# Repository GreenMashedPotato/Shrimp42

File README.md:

# Shrimp42(previously Kibod-01) Work In Progress

it's a keyboard inspired by [Slepet](https://github.com/ibnuda/Slepet) that has more stagger in some columns and only 3 thumb cluster keys instead of 5.

## Rev 1 (initial prototype)
Non Mirrored Keyboard uses 1 pro micro with 2x5 10pin IDC Connector:

Mirrored Keyboard, supports using 2 pro micros with trrs, or 1 pro micro with 2x5 10pin IDC Connector:

## Rev 2
Mirrored Keyboard Rev2(renamed to Shrimp42):

improvements from rev1:

* adds support for hotswap sockets
* adds support for smd diodes
* changed angles from 2 to 3 degrees while reducing distance between columns. 
* add board name: Shrimp 42
* add Stacked Acrylic Case

V1 vs V2

## Materials

| Qnty | Ref | Value | Description |
| --- | --- | --- | --- |
| 1 (2 if using trrs) | U1 | Arduino Pro-Micro ATmega32U4 |
| 42 | D-0-0 - D-3-5 | 1N4148 | Diode: 1N4148 (SOD 123 or THT)|
| 42 | K-0-0 - K-3-5 | MX or ALPS Switches | 1U |
| 42 (optional) | K-0-0 - K-3-5 | MX or ALPS Hotswap Sockets | this board supports the use of hotswap sockets and soldered connections |
| 2 | U2 | TRRS connectors OR 2x5 10pin IDC Connector |
| 1 | | TRRS Cable OR 2x5 10pin IDC Cable | used to connect both halves |
| 2 | | Shrimp42 pcb |
 
## Firmware
QMK and VIAL (provided via firmware but will need to sideload json and is untested) firmware for using the keyboard like in my setup above (using the extended GPIO pin to connect both halves and only 1 pro micro). [here](https://github.com/GreenMashedPotato/vial-qmk/tree/Shrimp42/keyboards/shrimp42).
 
QMK and VIAL for trrs connection (using 2 pro micros, slave board flipped, trrs connecting both sides) [here](https://github.com/GreenMashedPotato/vial-qmk/tree/Shrimp42/keyboards/shrimp42trrs)

## Library Used
[Keebio's footprints](https://github.com/keebio/Keebio-Parts.pretty)
[Ibnuda's footprints](https://github.com/ibnuda/rick-kicad-libs)

## Contact me:
Reddit [u/greenmashedpotato](https://www.reddit.com/user/greenmashedpotato)

## Disclaimer

I don't reccomend trying rev1 since the innermost and outermost column may be too far for some hands and can be tiring to use for long durations.

I haven't printed some of it. No guarantees that they work.

If things go wrong, I won't take any responisibilities, Try at your own risk.

## Additional Notes
After using the 2 in 1 diodes footprint, it may be too hard to know the orientation.
make sure the line on the diode is facing the square hole:

When using the Extended gpio pins to connect both halves, I have only tested using the pro micro on the left.

When using TRRS, dont forget to flip the right pro micro, I have only tested using the left pro micro as Master.

## License
GPL-3.0 License

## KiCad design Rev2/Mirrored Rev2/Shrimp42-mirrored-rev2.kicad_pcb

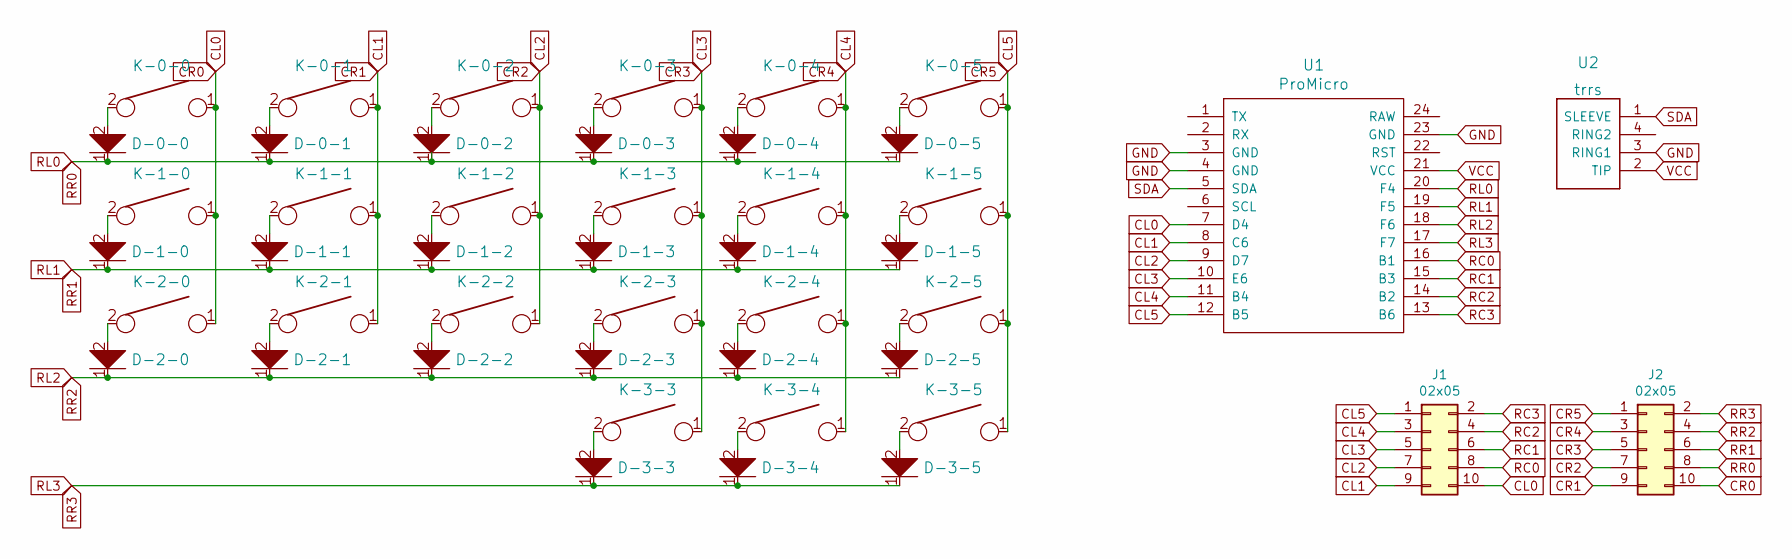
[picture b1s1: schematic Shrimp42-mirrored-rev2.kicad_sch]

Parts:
D-0-0, D-0-1, D-0-2, D-0-3, D-0-4, D-0-5, D-1-0, D-1-1, D-1-2, D-1-3, D-1-4, D-1-5, D-2-0, D-2-1, D-2-2, D-2-3, D-2-4, D-2-5, D-3-3, D-3-4, D-3-5: D; Diode-dual
J1, J2: 02x05; connector-shrouded
K-0-0, K-0-1, K-0-2, K-0-3, K-0-4, K-0-5, K-1-0, K-1-1, K-1-2, K-1-3, K-1-4, K-1-5, K-2-0, K-2-1, K-2-2, K-2-3, K-2-4, K-2-5, K-3-3, K-3-4, K-3-5: KEYSW; 100-dual-socket
U1: ProMicro; promicro
U2: trrs

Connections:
CL0: J1.10, J2.10, K-0-0.1, K-1-0.1, K-2-0.1, U1.7 (D4)
CL1: J1.9, J2.9, K-0-1.1, K-1-1.1, K-2-1.1, U1.8 (C6)
CL2: J1.7, J2.7, K-0-2.1, K-1-2.1, K-2-2.1, U1.9 (D7)
CL3: J1.5, J2.5, K-0-3.1, K-1-3.1, K-2-3.1, K-3-3.1, U1.10 (E6)
CL4: J1.3, J2.3, K-0-4.1, K-1-4.1, K-2-4.1, K-3-4.1, U1.11 (B4)
CL5: J1.1, J2.1, K-0-5.1, K-1-5.1, K-2-5.1, K-3-5.1, U1.12 (B5)
GND: U1.3 (GND), U1.4 (GND), U1.23 (GND), U2.3 (RING1)
unnamed: D-0-0.2, K-0-0.2
unnamed: D-0-1.2, K-0-1.2
unnamed: D-0-2.2, K-0-2.2
unnamed: D-0-3.2, K-0-3.2
unnamed: D-0-4.2, K-0-4.2
unnamed: D-0-5.2, K-0-5.2
unnamed: D-1-0.2, K-1-0.2
unnamed: D-1-1.2, K-1-1.2
unnamed: D-1-2.2, K-1-2.2
unnamed: D-1-3.2, K-1-3.2
unnamed: D-1-4.2, K-1-4.2
unnamed: D-1-5.2, K-1-5.2
unnamed: D-2-0.2, K-2-0.2
unnamed: D-2-1.2, K-2-1.2
unnamed: D-2-2.2, K-2-2.2
unnamed: D-2-3.2, K-2-3.2
unnamed: D-2-4.2, K-2-4.2
unnamed: D-2-5.2, K-2-5.2
unnamed: D-3-3.2, K-3-3.2
unnamed: D-3-4.2, K-3-4.2
unnamed: D-3-5.2, K-3-5.2
RC0: J1.8, U1.16 (B1)
RC1: J1.6, U1.15 (B3)
RC2: J1.4, U1.14 (B2)
RC3: J1.2, U1.13 (B6)
RL0: D-0-0.1, D-0-1.1, D-0-2.1, D-0-3.1, D-0-4.1, D-0-5.1, J2.8, U1.20 (F4)
RL1: D-1-0.1, D-1-1.1, D-1-2.1, D-1-3.1, D-1-4.1, D-1-5.1, J2.6, U1.19 (F5)
RL2: D-2-0.1, D-2-1.1, D-2-2.1, D-2-3.1, D-2-4.1, D-2-5.1, J2.4, U1.18 (F6)
RL3: D-3-3.1, D-3-4.1, D-3-5.1, J2.2, U1.17 (F7)
SDA: U1.5 (SDA), U2.1 (SLEEVE)
VCC: U1.21 (VCC), U2.2 (TIP)

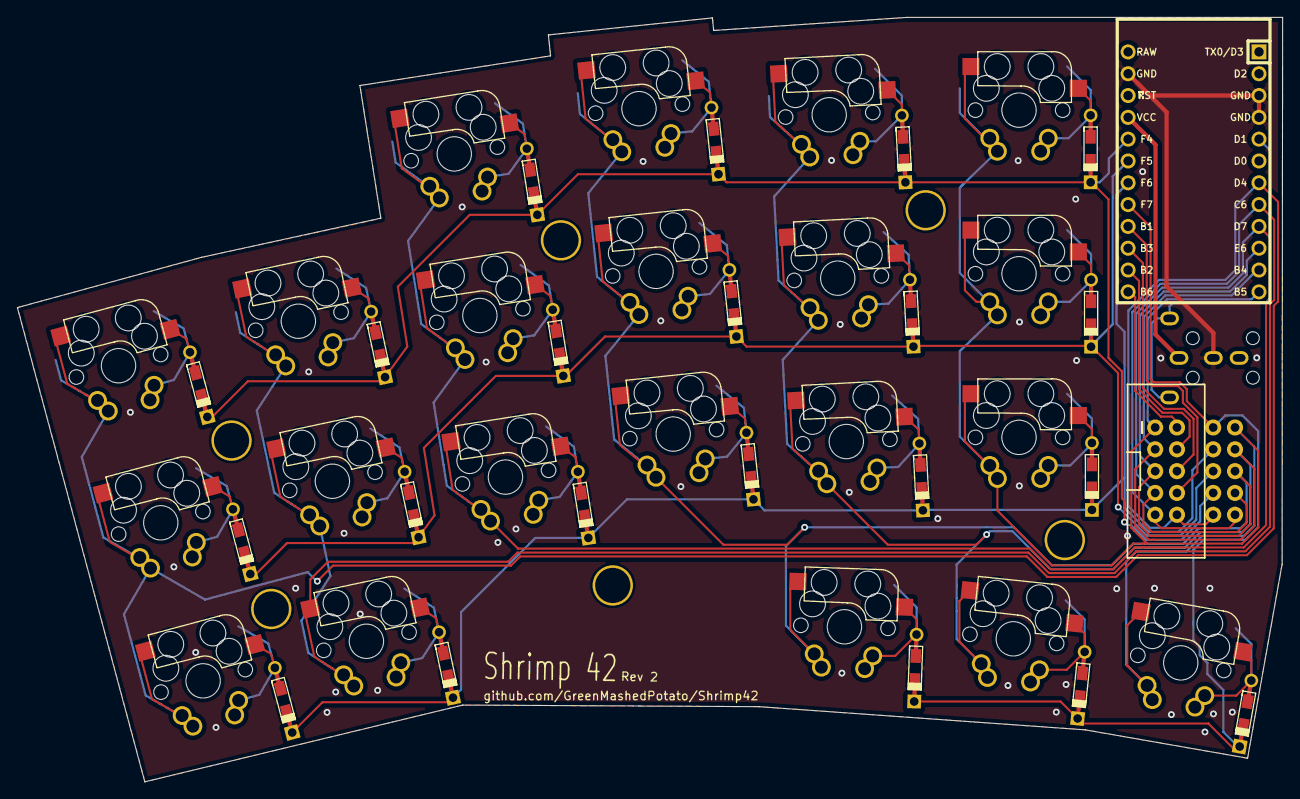
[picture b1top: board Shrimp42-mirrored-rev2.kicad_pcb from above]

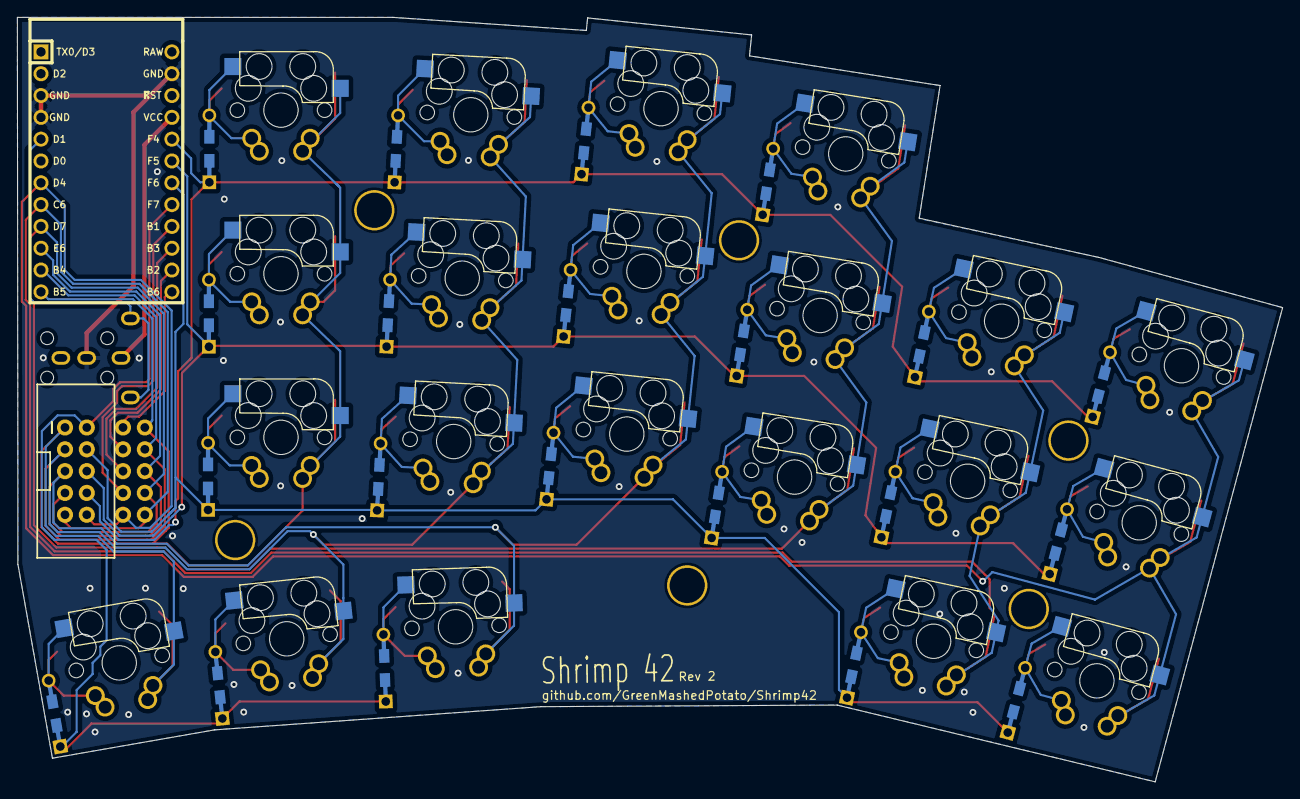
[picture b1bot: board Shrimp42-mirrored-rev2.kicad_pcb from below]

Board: 2 copper layers, 147.3 x 89.0 mm, 52 parts (2 on the bottom side), 38 nets.

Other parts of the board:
Ref**1, Ref**2, Ref**3, Ref**4, Ref**5, Ref**6: Val**; HOLE_M2_TH

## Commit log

2022-01-05 First Design
2022-01-05 add gerber
2022-01-05 fix outline issue
2022-01-05 add readme
2022-01-05 cleanup svgs
2022-01-05 add copper layer
2022-01-05 fix minor issues
2022-01-05 add warning
2022-01-05 move files to default folder
2022-01-05 add mirrored
2022-01-05 fix gerber error jlcpcb
2022-01-06 Create LICENSE
2022-01-06 add mirror to readme
2022-01-06 fix typo
2022-01-17 renamed mirrored
2022-01-25 fixed non reversible holes
2022-01-29 update gerber and readme
2022-01-29 add more detail to readme
2022-01-29 update gitignore
2022-01-29 removed case svg, will readd after fixing it.
2022-01-31 update readme, working on rev2
2022-02-04 add rev2
2022-02-05 add name and icon, add mounting holes, add trrs support back
2022-02-05 cleanup some wiring
2022-02-06 update readme, update wiring
2022-02-06 add support for smd diodes
2022-02-07 fixed and straightened some wirings
2022-02-08 added case, update readme
2022-02-09 restructure repo
2022-02-11 update shrimp image to be smaller
2022-02-11 update firmware in readme
2022-02-12 add firmware for trrs in readme
2022-02-12 update thumb cluster since its too close to amphenol cutout
2022-02-16 update readme, update icon
2022-02-16 update rev1 vs rev2 image
2022-02-26 rewired board. change pcb holes. push commit before order pcb
2022-08-07 add acrylic case
